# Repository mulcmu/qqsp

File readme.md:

### Collection of my FLSUN QQ-S Pro projects:

##### Wifi breakout board and buzzer

A small pcb to fit the mks wifi socket on the stock main board.  Includes a passive buzzer and header footprints to access the MCU gpio for wiring up mods.  This keeps the wiring tidy.

)

##### Capacitive Nozzle Probe

Concept probe to use capacitive touch input on an ESP32-S3 triggered by nozzle contact.  Working pretty well.

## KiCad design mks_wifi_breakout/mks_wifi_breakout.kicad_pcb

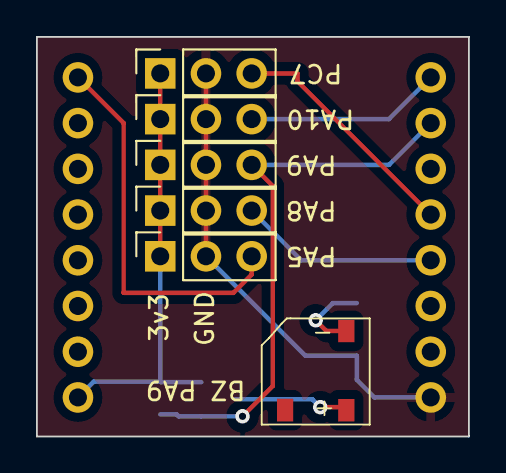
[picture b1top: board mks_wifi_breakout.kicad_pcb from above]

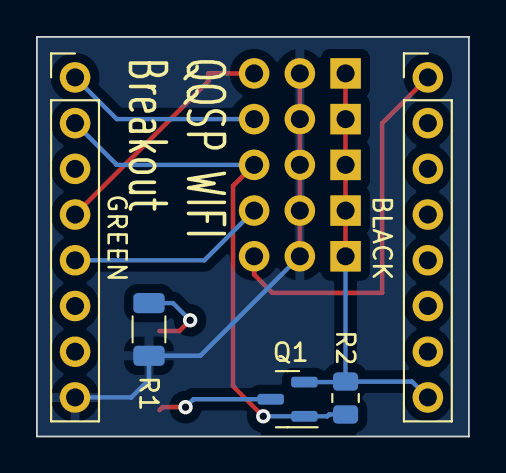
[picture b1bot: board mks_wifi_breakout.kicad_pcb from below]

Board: 2 copper layers, 24.0 x 22.2 mm, 11 parts (5 on the bottom side), 9 nets.

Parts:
BLACK: Conn_01x08; PinHeader_1x08_P2.54mm_Vertical
BZ1: 5020 Passive; 5020passiveBuzzer
GREEN: Conn_01x08; PinHeader_1x08_P2.54mm_Vertical
PA5, PA8, PA9, PA10: Conn_01x03; PinSocket_1x03_P2.54mm_Vertical
PC7: Conn_01x03; PinSocket_1x03_P2.54mm_Vertical
Q1: AO3401A; SOT-23
R1: 0; R_1206_3216Metric
R2: 10k; R_0805_2012Metric

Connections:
+3V3: BLACK.8, PA5.1, PA8.1, PA9.1, PA10.1, PC7.1, Q1.2 (S), R2.2
/IO0: GREEN.5, PA8.3
/IO1: GREEN.4, PC7.3
/PA5: BLACK.1, PA5.3
/PA9: GREEN.2, PA9.3, Q1.1 (G), R2.1
/PA10: GREEN.1, PA10.3
GND: GREEN.8, PA5.2, PA8.2, PA9.2, PA10.2, PC7.2, R1.1
unnamed: BZ1.1 (+), Q1.3 (D)
unnamed: BZ1.2 (-), R1.2

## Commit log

2024-10-06 add wifi pcb
2024-10-12 add cap probe
